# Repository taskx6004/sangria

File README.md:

# sangria
Raspberry Pi Zero based handheld computer

It's basically a TI's USB 1s lithium battery charger to provide both buck and boost switching functions, to simplify the power design. The LCD is connected default SPI arrangement (SPI0), and keyboard is a USB HID device to provide user input.

## Initial commit
This version has a working keyboard based on BBQ10 with RP2040 by running modified version firmware from https://github.com/solderparty/i2c_puppet

### Known Issues:
- BQ25616 needs OTG pin strobe to GND to initialized battery charge, as this pin has already pulled high, thus to boost battery voltage to 5V.
- USB traces are inverted, the symbol for RPI part has the pin number inverted, thus a PCB trace rework is required.
- BQ25616 can pull 7.5v from some high power USB charger, Pi Zero power IC will emit the magic smoke in minutes...
- Keyboard LED MOSFET gate pin is not connected.

### What's next
- Add a USB hub chip to hook more RP2040 with B2B connector to house peripherals
- Add a nrf52840 to house Meshtastic device, with small OLED and GPS
- Replace BQ25616 and drop a DC/DC to PMID output, to prevent fry your Pi Zero, and you can hook a 4s model lithium battery pack
- Add a jog dial to keyboard chip, to implement tab/up arrow/down arrow key, as command line auto completion and history function

## How to build firmware
Refer to i2c-puppet building guide. As pico SDK is included in the repo, git pull will consume 900M traffic, you have been warned. After pulling the repo, replace files in `app` folder, and add new file in `boards` directory. cmake command is changed to:

`cmake -DPICO_BOARD=bbq10kbd_breakout -DCMAKE_BUILD_TYPE=Debug ..`

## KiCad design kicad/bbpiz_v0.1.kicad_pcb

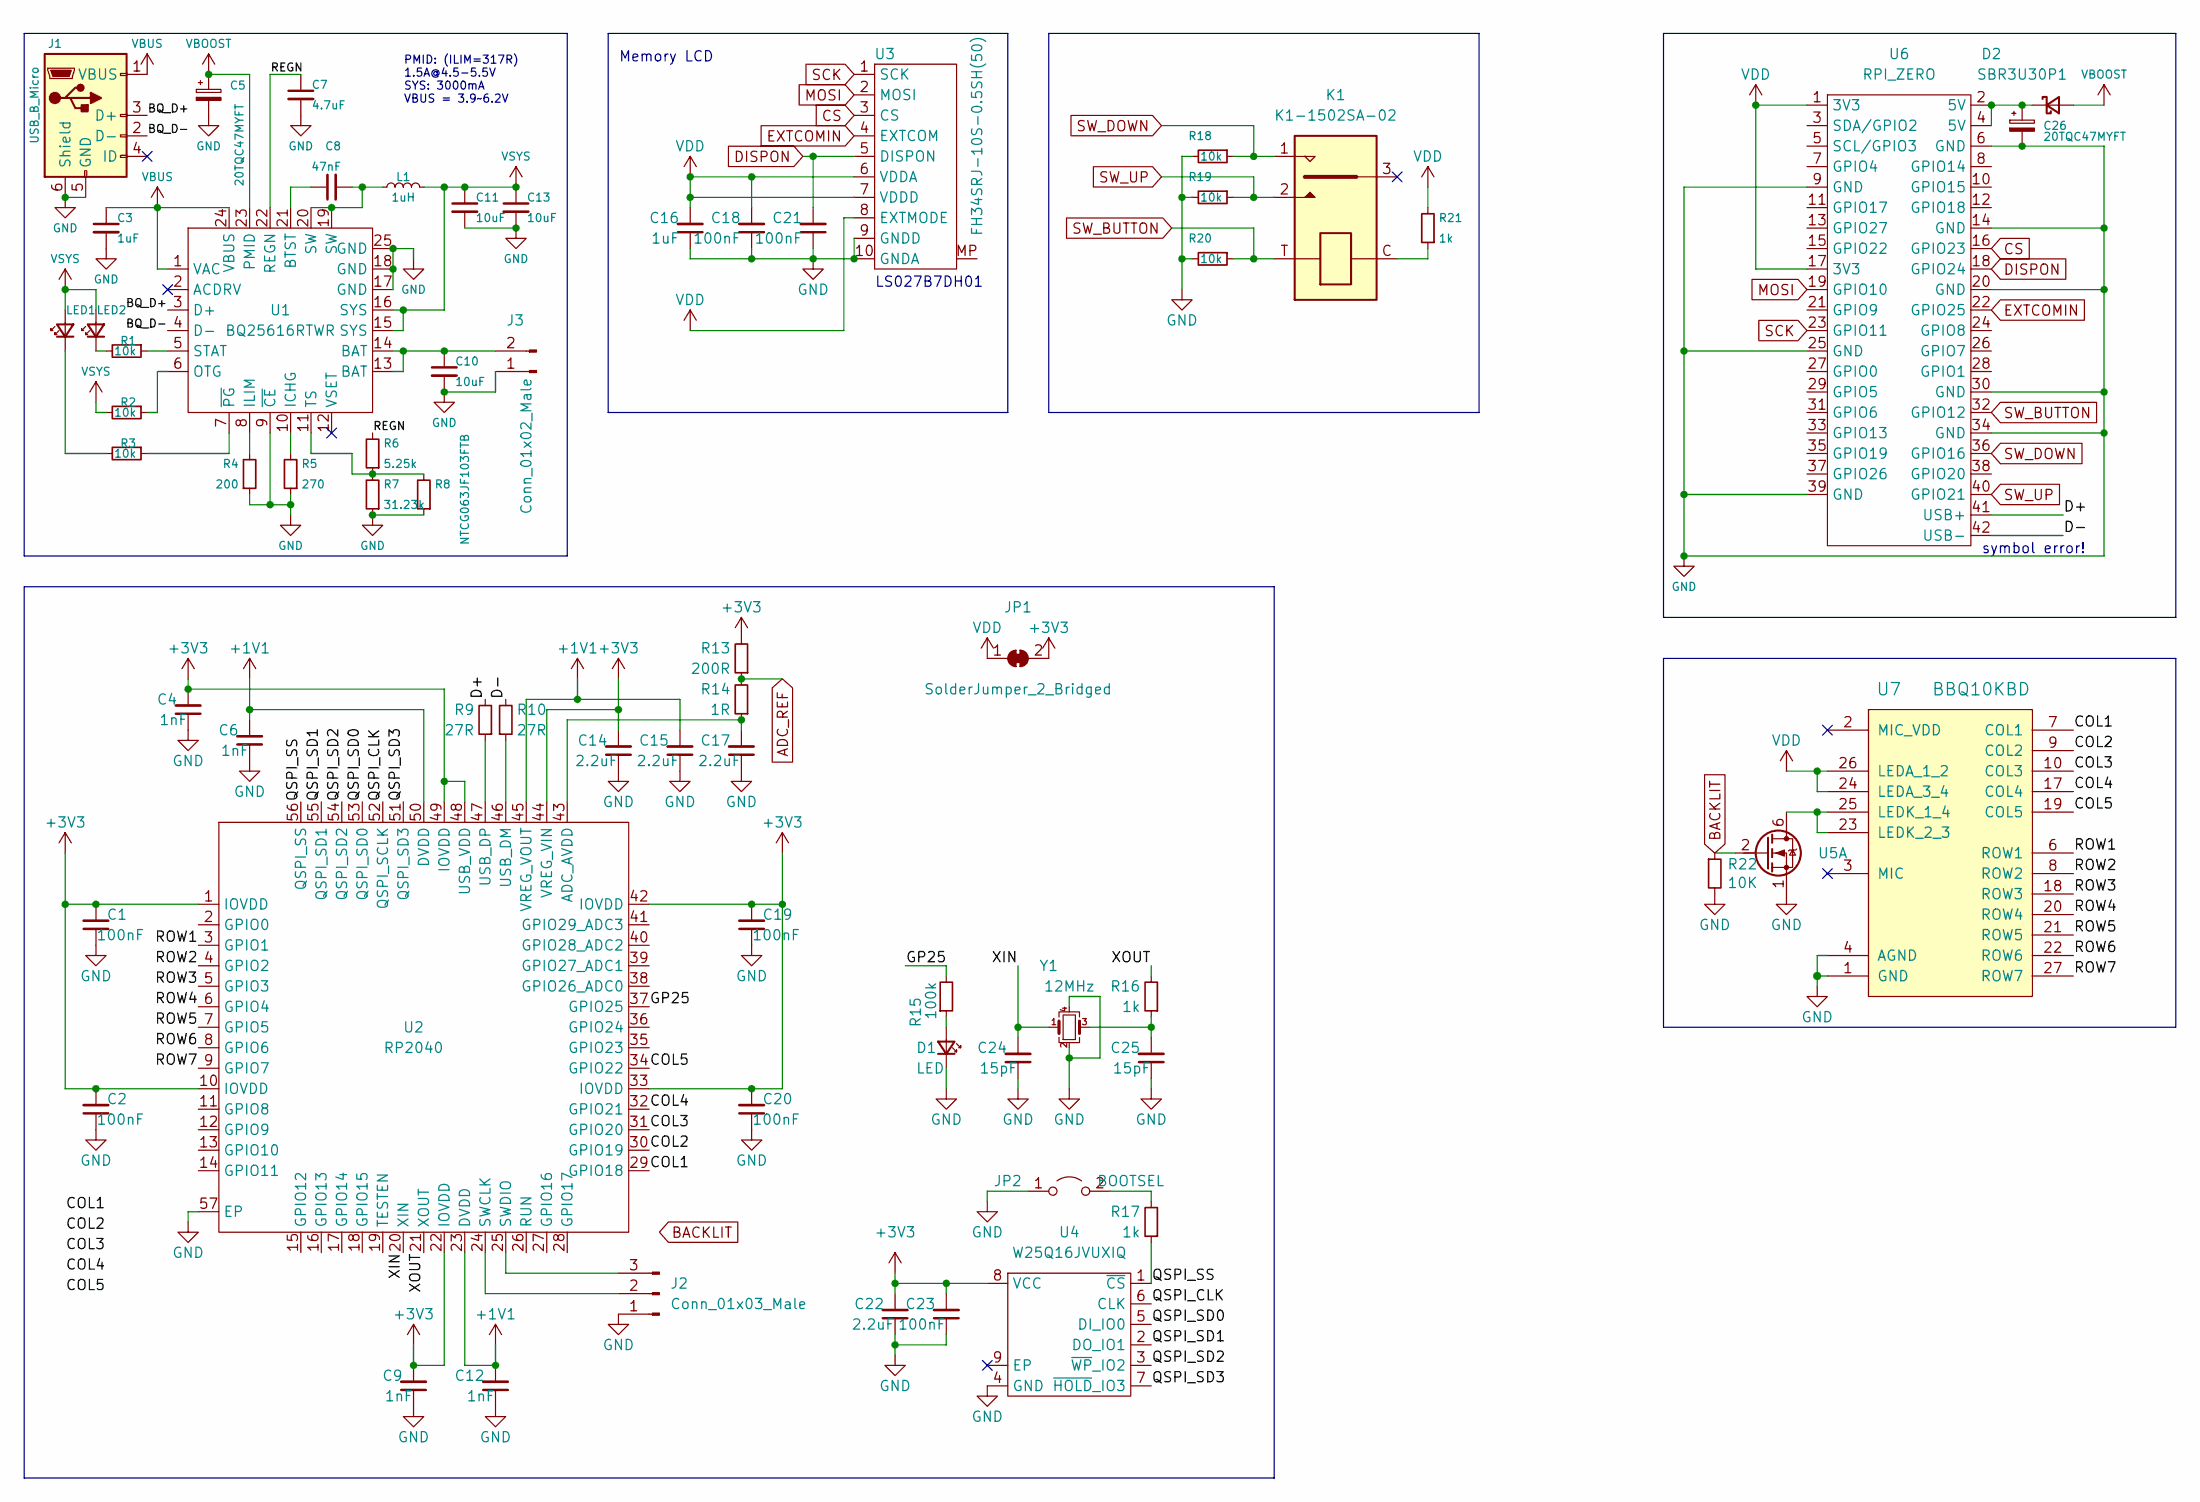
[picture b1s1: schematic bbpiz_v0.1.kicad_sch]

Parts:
C1, C2, C18, C19, C20, C21, C23: 100nF; C_0201_0603Metric
C3: 1uF; C_0603_1608Metric
C4, C6, C9, C12: 1nF; C_0201_0603Metric
C5, C26: 20TQC47MYFT
C7: 4.7uF; C_0402_1005Metric
C8: 47nF; C_0402_1005Metric
C10, C11, C13: 10uF; C_0603_1608Metric
C14, C15, C17, C22: 2.2uF; C_0402_1005Metric
C16: 1uF; C_0402_1005Metric
C24, C25: 15pF; C_0201_0603Metric
D1: LED; LED_0603_1608Metric
D2: SBR3U30P1; D_PowerDI-123
J1: USB_B_Micro; 474910001
J2: Conn_01x03_Male; PinHeader_1x03_P1.27mm_Vertical
J3: Conn_01x02_Male; HJX522365
JP1: SolderJumper_2_Bridged; SolderJumper-2_P1.3mm_Bridged_RoundedPad1.0x1.5mm
JP2: BOOTSEL; SolderJumper-2_P1.3mm_Open_RoundedPad1.0x1.5mm
K1: K1-1502SA-02
L1: 1uH; WIP252010P-1R0ML
LED1: LED; LED_0603_1608Metric
LED2: LED_RED_0603; LED_0603_1608Metric
R1, R2, R3, R18, R19, R20: 10k; R_0201_0603Metric
R4: 200; R_0201_0603Metric
R5: 270; R_0201_0603Metric
R6: 5.25k; R_0201_0603Metric
R7: 31.23k; R_0201_0603Metric
R8: NTCG063JF103FTB; R_0201_0603Metric
R9, R10: 27R; R_0201_0603Metric
R13: 200R; R_0201_0603Metric
R14: 1R; R_0201_0603Metric
R15: 100k; R_0201_0603Metric
R16, R17, R21: 1k; R_0201_0603Metric
R22: 10K; R_0201_0603Metric
U1: BQ25616RTWR; QFN-24-1EP_4x4mm_P0.5mm_EP2.7x2.7mm_ThermalVias
U2: RP2040
U3: FH34SRJ-10S-0.5SH(50)
U4: W25Q16JVUXIQ
U5: SIA517DJ-T1-GE3; Vishay_PowerPAK_SC70-6L_Dual
U6: RPI_ZERO; PI-ZERO_USB
U7: BBQ10KBD; BM14B(0.8)-24DS-0.4V(53)
Y1: 12MHz; Crystal_SMD_2520-4Pin_2.5x2.0mm

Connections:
+1V1: C6.2, C12.2, C15.2, U2.23 (DVDD), U2.45 (VREG_VOUT), U2.50 (DVDD)
+3V3: C1.2, C2.2, C4.2, C9.2, C14.2, C19.2, C20.2, C22.2, C23.2, JP1.2 (B), R13.2, U2.1 (IOVDD), U2.10 (IOVDD), U2.22 (IOVDD), U2.33 (IOVDD), U2.42 (IOVDD), U2.44 (VREG_VIN), U2.48 (USB_VDD), U2.49 (IOVDD), U4.8 (VCC)
/BQ_D+: J1.3 (D+), U1.3 (D+)
/BQ_D-: J1.2 (D-), U1.4 (D-)
/COL1: U2.29 (GPIO18), U7.7 (COL1)
/COL2: U2.30 (GPIO19), U7.9 (COL2)
/COL3: U2.31 (GPIO20), U7.10 (COL3)
/COL4: U2.32 (GPIO21), U7.17 (COL4)
/COL5: U2.34 (GPIO22), U7.19 (COL5)
/D+: R9.2, U6.41 (USB+)
/D-: R10.2, U6.42 (USB-)
/GP25: R15.2, U2.37 (GPIO25)
/QSPI_CLK: U2.52 (QSPI_SCLK), U4.6 (CLK)
/QSPI_SD0: U2.53 (QSPI_SD0), U4.5 (DI_IO0)
/QSPI_SD1: U2.55 (QSPI_SD1), U4.2 (DO_IO1)
/QSPI_SD2: U2.54 (QSPI_SD2), U4.3 (~WP_IO2)
/QSPI_SD3: U2.51 (QSPI_SD3), U4.7 (~HOLD_IO3)
/QSPI_SS: R17.1, U2.56 (QSPI_SS), U4.1 (~CS)
/REGN: C7.1, R6.2, U1.22 (REGN)
/ROW1: U2.3 (GPIO1), U7.6 (ROW1)
/ROW2: U2.4 (GPIO2), U7.8 (ROW2)
/ROW3: U2.5 (GPIO3), U7.18 (ROW3)
/ROW4: U2.6 (GPIO4), U7.20 (ROW4)
/ROW5: U2.7 (GPIO5), U7.21 (ROW5)
/ROW6: U2.8 (GPIO6), U7.22 (ROW6)
/ROW7: U2.9 (GPIO7), U7.27 (ROW7)
/XIN: C24.2, U2.20 (XIN), Y1.1
/XOUT: R16.2, U2.21 (XOUT)
ADC_REF: R13.1, R14.2
BACKLIT: R22.1, U5.2
CS: U3.3 (CS), U6.16 (GPIO23)
DISPON: C21.2, U3.5 (DISPON), U6.18 (GPIO24)
EXTCOMIN: U3.4 (EXTCOM), U6.22 (GPIO25)
GND: C1.1, C2.1, C3.2, C4.1, C5.2, C6.1, C7.2, C9.1, C10.2, C11.2, C12.1, C13.2, C14.1, C15.1, C16.1, C17.1, C18.1, C19.1, C20.1, C21.1, C22.1, C23.1, C24.1, C25.1, C26.2, D1.1 (K), J1.5 (GND), J1.6 (Shield), J2.1, J3.1, JP2.1 (A), R4.1, R5.1, R7.1, R8.1, R18.2, R19.2, R20.2, R22.2, U1.9 (~CE), U1.17 (GND), U1.18 (GND), U1.25 (GND), U2.57 (EP), U3.9 (GNDD), U3.10 (GNDA), U4.4 (GND), U5.1, U6.6 (GND), U6.9 (GND), U6.14 (GND), U6.20 (GND), U6.25 (GND), U6.30 (GND), U6.34 (GND), U6.39 (GND), U7.1 (GND), U7.4 (AGND), U7.5 (GND), U7.11 (GND), U7.12 (GND), U7.13 (GND), U7.14 (GND), U7.15 (GND), U7.16 (GND), U7.28 (GND), Y1.2, Y1.4
MOSI: U3.2 (MOSI), U6.19 (GPIO10)
unnamed: C8.1, U1.21 (BTST)
unnamed: C8.2, L1.1, U1.19 (SW), U1.20 (SW)
unnamed: C10.1, J3.2, U1.13 (BAT), U1.14 (BAT)
unnamed: C17.2, R14.1, U2.43 (ADC_AVDD)
unnamed: C25.2, R16.1, Y1.3
unnamed: C26.1, D2.1 (K), U6.2 (5V), U6.4 (5V)
unnamed: D1.2 (A), R15.1
unnamed: J2.2, U2.24 (SWCLK)
unnamed: J2.3, U2.25 (SWDIO)
unnamed: JP2.2 (B), R17.2
unnamed: K1.C, R21.1
unnamed: LED1.1 (K), R3.2
unnamed: LED2.1 (K), R1.2
unnamed: R1.1, U1.5 (STAT)
unnamed: R2.1, U1.6 (OTG)
unnamed: R3.1, U1.7 (~PG)
unnamed: R4.2, U1.8 (ILIM)
unnamed: R5.2, U1.10 (ICHG)
unnamed: R6.1, R7.2, R8.2, U1.11 (TS)
unnamed: R9.1, U2.47 (USB_DP)
unnamed: R10.1, U2.46 (USB_DM)
unnamed: U5.6, U7.23 (LEDK_2_3), U7.25 (LEDK_1_4)
SCK: U3.1 (SCK), U6.23 (GPIO11)
SW_BUTTON: K1.T, R20.1, U6.32 (GPIO12)
SW_DOWN: K1.1, R18.1, U6.36 (GPIO16)
SW_UP: K1.2, R19.1, U6.40 (GPIO21)
VBOOST: C5.1, D2.2 (A), U1.23 (PMID)
VBUS: C3.1, J1.1 (VBUS), U1.1 (VAC), U1.24 (VBUS)
VDD: C16.2, C18.2, JP1.1 (A), R21.2, U3.6 (VDDA), U3.7 (VDDD), U3.8 (EXTMODE), U6.1 (3V3), U6.17 (3V3), U7.24 (LEDA_3_4), U7.26 (LEDA_1_2)
VSYS: C11.1, C13.1, L1.2, LED1.2 (A), LED2.2 (A), R2.2, U1.15 (SYS), U1.16 (SYS)

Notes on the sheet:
symbol error!
LS027B7DH01
Memory LCD
PMID: (ILIM=317R) 1.5A@4.5-5.5V SYS: 3000mA VBUS = 3.9~6.2V

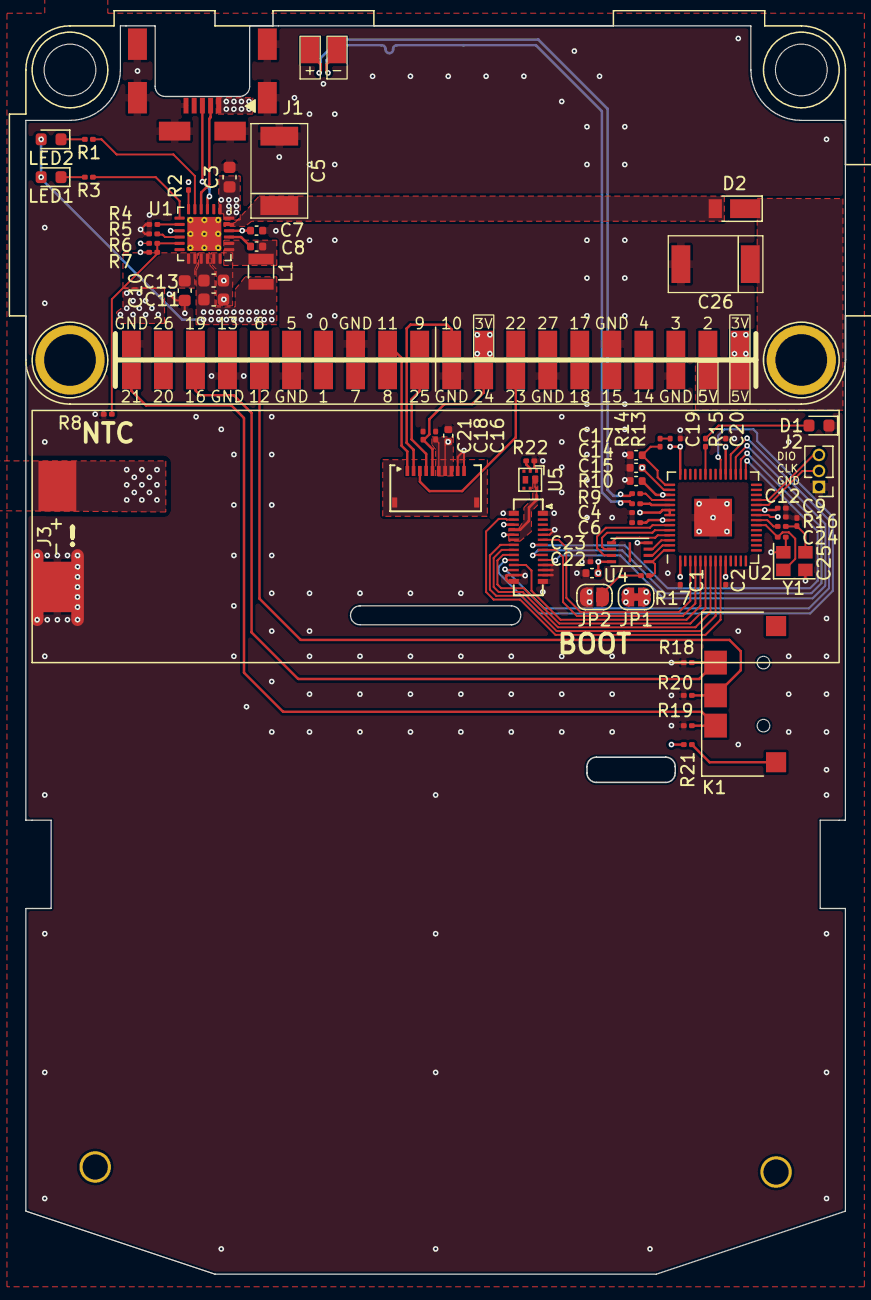
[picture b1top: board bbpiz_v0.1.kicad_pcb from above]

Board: 4 copper layers, 65.0 x 99.0 mm, 65 parts (0 on the bottom side), 65 nets.

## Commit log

2022-06-25 Update README.md
    - fix typos
    - added 2 known issus
